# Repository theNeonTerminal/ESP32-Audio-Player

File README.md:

# ESP32 Based Audio Player

An ESP32 Based iPod type music player, can play music (`.mp3`) stored and given in an SD Card along with OLED display to show stats

---

## About this Project

An ESP32 (my favourite microcontroller) based music player - similar to an iPod, but DIY and made for a lot cheaper. Right now the current version of the firmware only includes wired headphones (via PCM5102a DAC module) but I plan to implement a Bluetooth A2DP sink and source so that it is different from a normal iPod.

## Hardware Design

### 01 / Circuit Schematic

<div align="center">

</div>

### 02 / PCB Layout

<div align="center">

> [!IMPORTANT]
> It might look like overlapping footprints, but female header pins should be used on the ESP32 and OLED display to raise the height by a little and make enough space on the components, the actual holes dont overlap so its safe to use.

</div>

### 03 / PCB 3D View

<div align="center">

</div>

> [!IMPORTANT]
> The PCM5102a DAC module must have this SCK bridge soldered on the front side and this very particular configuration on the back side for it properly get into I2S mode, else you might have a fully silent output

---

## Currently Implemented Features

* **Wired:** No wireless connectivity issues! No latency issues!
* **SD Card:** Update your SD card and it works without needing to update the firmware again.
* **OLED Feedback:** OLED display to show currently playing song and if it's paused or not.
* **Physical control buttons:** Control your sound using clicky Cherry MX Blue mechanical switches.

---

## BoM

| PART | QUANTITY | Purpose |
| ---- | -------- | ------- |
| ESP32 | 1 | Main Processing unit |
| PCM5102a | 1 | Main I2S DAC |
| SPI SD Card Reader | 1 | To read the SD Card |
| Professional PCB | 1 | To house the electronics |
| OLED SSD1306 | 1 | To display some stats about the song |
| Mechanical switches | 3 | For audio controls |
| Battery | 1 | To power the device |
| Professional PCB | 1 | To house the electronics |

---

### SD Card Formatting

1. Format your SD card into FAT32 (can be done using Windows built in formatting tool for card 32GB or less, for larger cards, try using 3rd party tools like MiniTool Partition Wizard)
2. Put your favourite `.mp3` songs into the SD card, and make sure the file names are not too long, for the text might overflow on the OLED display.
3. Paths dont really matter, like your song can be insider many folders, and it finds them all.
4. Enjoy ;)

---

## Firmware Working

Dependencies:

* <a href="https://github.com/pschatzmann/arduino-audio-tools">https://github.com/pschatzmann/arduino-audio-tools</a> (arduino-audio-tools)
* <a href="https://github.com/pschatzmann/codec-helix">https://github.com/pschatzmann/codec-helix</a> (codec-helix)
* <a href="https://github.com/adafruit/adafruit-gfx-library">https://github.com/adafruit/adafruit-gfx-library</a> (adafruit-gfx-library)
* <a href="https://github.com/adafruit/adafruit_ssd1306">https://github.com/adafruit/adafruit_ssd1306</a> (adafruit_ssd1306)

This code runs a modified version of an <a href="https://github.com/pschatzmann/arduino-audio-tools/tree/main/examples/examples-player/player-sd-i2s">this</a> example code. I have added custom defined I2S and SPI pins (CS only for SPI) and added some graphics for OLED SSD1306 driver. I display the currently playing song on the OLED display and implement a simple logic to handle button presses to control the audio from the `player` class (please refer to arduino-audio-tools documentation for this) which include `next-track`, `previous-track` and pause (`isActive`)

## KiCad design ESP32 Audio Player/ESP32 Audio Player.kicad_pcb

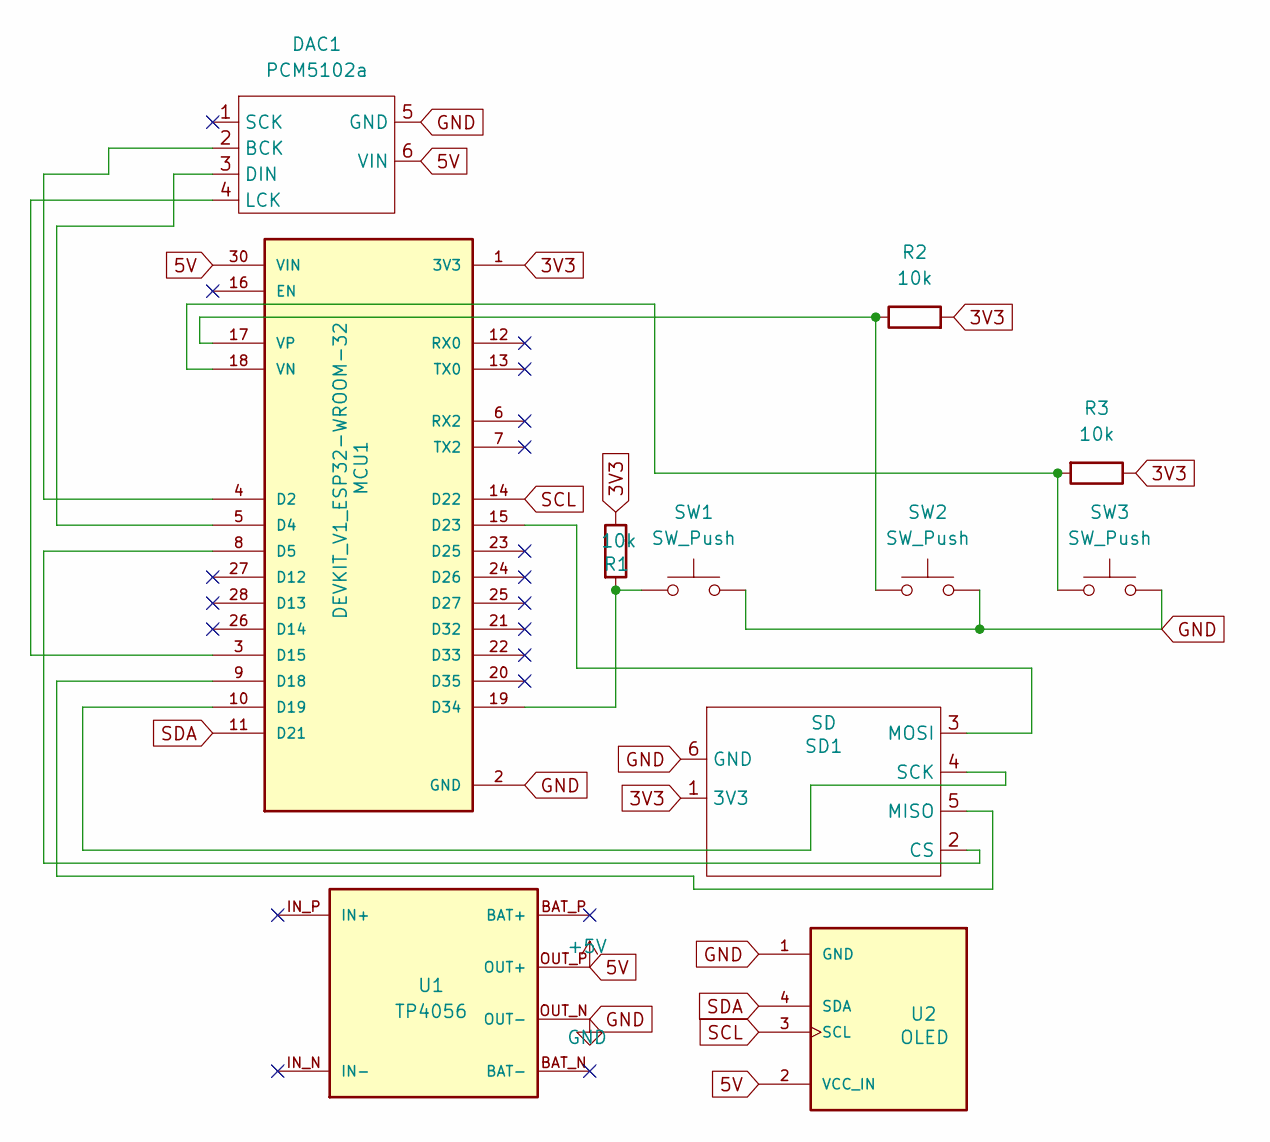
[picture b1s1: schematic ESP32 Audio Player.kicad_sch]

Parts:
DAC1: PCM5102a; GY-PCM5102
MCU1: DEVKIT_V1_ESP32-WROOM-32; ESP32-30-pin
R1, R2, R3: 10k; R_Axial_DIN0204_L3.6mm_D1.6mm_P7.62mm_Horizontal
SD1: SD; MODULE_MICROSD_SPI_OR_SDIO_CARD
SW1, SW2, SW3: SW_Push; SW_Cherry_MX_PCB_1.00u
U1: TP4056; MODULE_TP4056_MICRO-USB_CHARGER_-_1A
U2: OLED; OLED-SSD1306; PARTREV 2018-09-10

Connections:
3V3: MCU1.1 (3V3), R1.1, R2.2, R3.1, SD1.1 (3V3)
5V: DAC1.6 (VIN), MCU1.30 (VIN), U1.OUT_P (OUT+), U2.2 (VCC_IN)
GND: DAC1.5 (GND), MCU1.2 (GND), MCU1.29 (GND), SD1.6 (GND), SW1.2, SW2.2, SW3.2, U1.OUT_N (OUT-), U2.1 (GND)
unnamed: DAC1.2 (BCK), MCU1.4 (D2)
unnamed: DAC1.3 (DIN), MCU1.5 (D4)
unnamed: DAC1.4 (LCK), MCU1.3 (D15)
unnamed: MCU1.8 (D5), SD1.2 (CS)
unnamed: MCU1.9 (D18), SD1.5 (MISO)
unnamed: MCU1.10 (D19), SD1.4 (SCK)
unnamed: MCU1.15 (D23), SD1.3 (MOSI)
unnamed: MCU1.19 (D34), R1.2, SW1.1
unnamed: MCU1.18 (VN), R3.2, SW3.1
unnamed: MCU1.17 (VP), R2.1, SW2.1
SCL: MCU1.14 (D22), U2.3 (SCL)
SDA: MCU1.11 (D21), U2.4 (SDA)

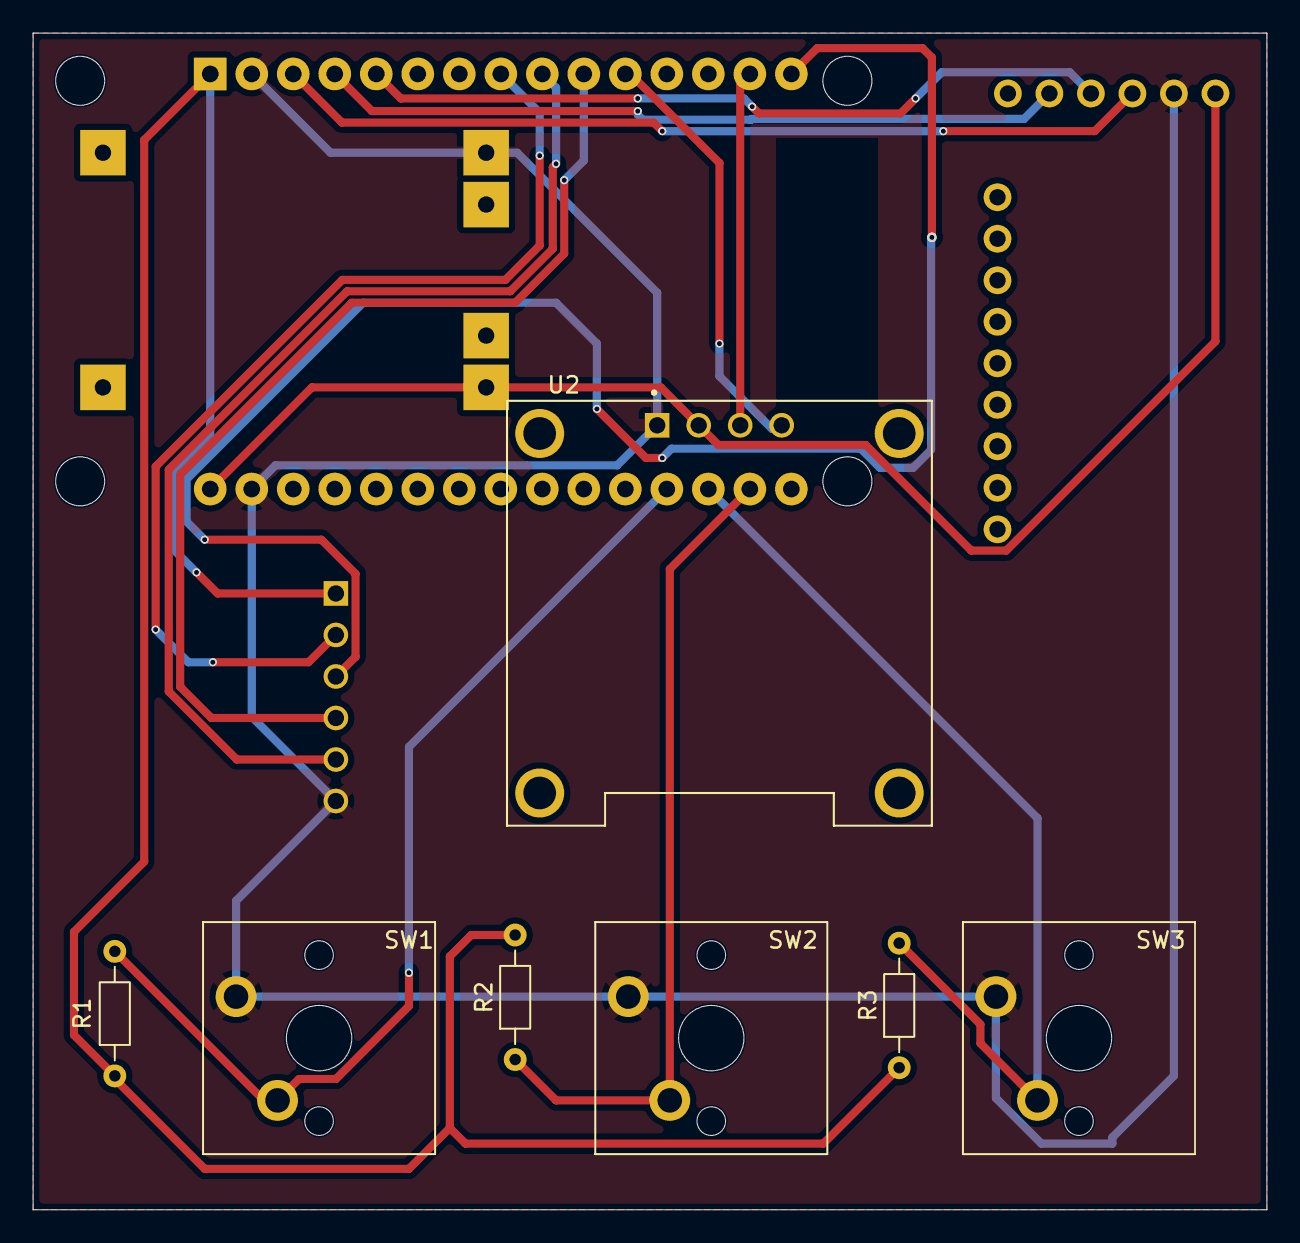
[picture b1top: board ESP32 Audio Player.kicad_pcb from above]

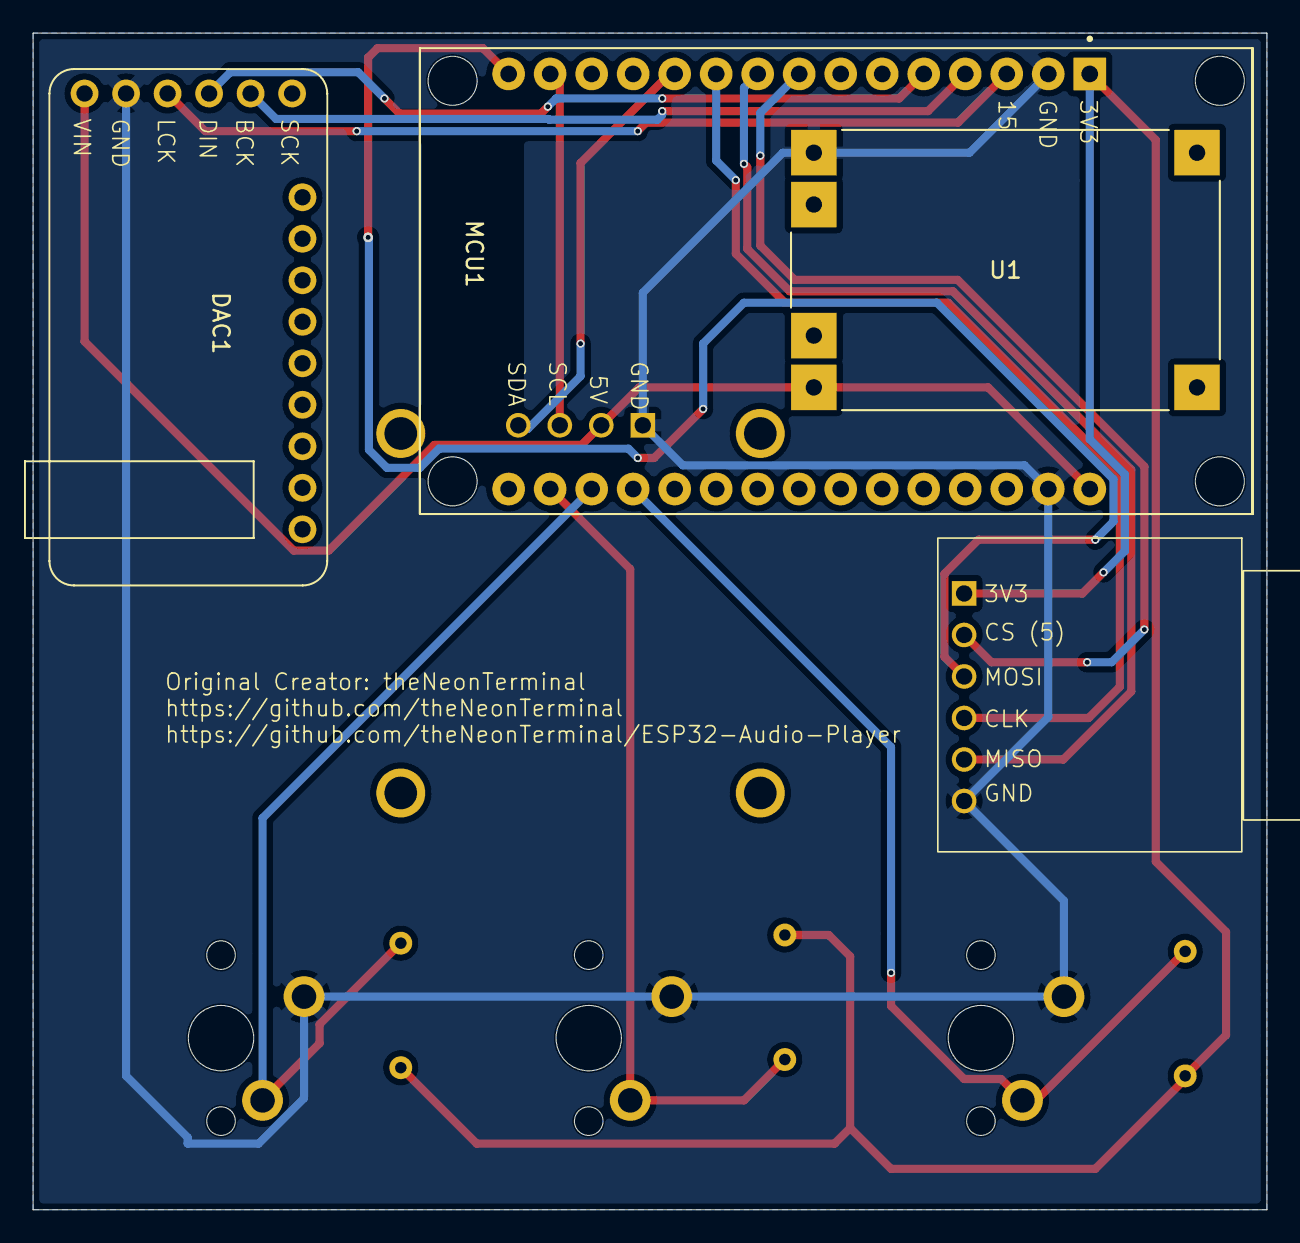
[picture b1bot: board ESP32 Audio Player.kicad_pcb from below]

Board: 2 copper layers, 75.5 x 72.0 mm, 11 parts (4 on the bottom side), 15 nets.

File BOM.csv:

Item,Qty,Supplier,Cost/item,Total Cost,link
SD Card Reader Module,1,amazon.in,$1.20,$1.20,https://www.amazon.in/RobomallsTM-Micro-Module-Aiduino-Inter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
ESP32 WROOM,1,amazon.in,$5.20,$5.20,https://www.amazon.in/gp/product/B0HD7QC26L/ref=ewc_pr_img_2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
Battery,1,amazon.in,$1.10,$1.10,https://www.amazon.in/gp/product/B0HC6RRYJL/ref=ox_sc_act_ti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
Mechanical Switches,1,amazon.in,$5.30,$5.30,https://www.amazon.in/gp/product/B0H1X4CW7W/ref=ox_sc_act_im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
PCB,1,jlcpcb.com,$13.50,$13.50,https://jlcpcb.com
PCM5102a,1,hubtronics.com,$4.70,$4.70,https://hubtronics.in/pcm5102-i2s-digital-audio-dac-decoder-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
TP4056 Charger,1,robu.in,$0.20,$0.20,https://robu.in/product/tp4056-1a-li-ion-lithium-battery-cha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
OLED SSD1306,1,robu.in,$2.70,$2.70,https://robu.in/product/0-96-oled-display-module/
Estimated total shipping,1,,,$4.00,
